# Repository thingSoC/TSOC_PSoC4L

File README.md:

# TSOC_PSoC4L - PSoC4 (Large) Embedded Module :

The TSOC_PSoC4L is a [PSoC4-Programmable System on Chip](http://www.cypress.com/documentation/datasheets/psoc-4-psoc-4200l-family-datasheet)
based board with integrated USB and Li-Po battery power and charging functions, 
in an Embedded Module format for the new thingSoC, Internet of Things open standard.

The TSOC_PSoC4L is a low cost, embeddable module featuring a PSoC4 "Large" device :

* 32-bit MCU Subsystem (48MHZ ARM Cortex-M0)
* USB Full-Speed Controller - 16 Endpoints
* Li-Po battery connector and integrated USB charger
* Programmable Analog Blocks (4 blocks)
* Programmable Digital Blocks (8 blocks)
* 3.3 Volt or 5.0 Volt Operation
* Serial Communication (3 Ports)
* Counter/Timers/PWMs (8 Ports)
* CAN (controller area network) Controller
* Battery Charge Status LED
* USER LED
* USER Pushbutton
* Optional 32Khz Oscillator for Real-Time Clock
* Optional High Precision Oscillator
* Optional FM24W256-G NVSRAM (32K Bytes Nonvolatile SRAM)
* [thingSoC Compliant Module](http://www.thingsoc.com)
* [Mikrobus Compatible Module](http://www.mikroe.com/mikrobus/) 

[TSOC_PSoC4L](https://github.com/thingSoC/TSOC_PSoC4L)

**thingSoC Reference Designs** are example thingSoC implementations that implement
various reference and testing circuits for demonstrating the use of the thingSoC libraries.
These reference designs can serve as starting templates for user designs.

---------------------------------------

## TSOC_PSoC4L Instructions

The TSOC_PSoC4L comes preprogrammed with a command line interpreter (CLI)
that runs on the enumerated USB COM port by default. It can be changed to
run onother ports interactively.

Immediately after plugging in the USB or Li-Po battery power the TSOC_PSoC4L will :

1) Runs a USB bootloader for ten (10) seconds to allow you to update the firmware.
   Use the [Cypress Bootloader Host](http://www.cypress.com/documentation/application-notes/an68272-psoc-3-psoc-4-psoc-5lp-and-psoc-analog-coprocessor-uart)
   to load new firmware into the device to customize it.

2) Runs the RSVP command line interpreter with the following commands :
  * commands : display the list of currenyl available commands
  * info : display the firmware revision number and other board details
  * echo : echo the current command
  * test adc : display all current ADC channel values
  * test uart : sends test string to all UART ports
  * test boot : run the bootloader
  * console x : changes the console to port "X"
  * connect x y : connect port x to port y until the user button is pressed to exit  
    where :  X (Y) = 
    0 - USB Port
    1 - UART1 Port
    2 - UART2 Port
    3 - I2C1 Port
    4 - I2C2 Port
    5 - SPI1 Port
    6 - SPI2 Port

---------------------------------------
## Other Applications

The TSOC_PSoC4L can also drive other devices, such as Servos, Motors, Relays and more.
This requires custom firmware at the current time.

---------------------------------------

## TSOC_PSoC4L Status <a name="TSOC_PSoC4L_status"/>

**11/06/2016:** 
Revision 1.0 - Initial Layout released to OSHpark

---------------------------------------
## TSOC_PSoC4L Model Images

[TSOC_PSoC4L](https://github.com/thingSoC/TSOC_PSoC4L)

[TSOC_PSoC4L](https://github.com/thingSoC/TSOC_PSoC4L)

---------------------------------------

## TSOC_PSoC4L Documentation Index <a name="TSOC_PSoC4L_documentation_index"/>

[TSOC_PSoC4L Project](http://thingsoc.github.io/projects/TSOC_PSoC4L.html)

[TSOC_PSoC4L Hardware](https://github.com/thingSoC/TSOC_PSoC4L/tree/master/TSOC_PSoC4L/hardware)

---------------------------------------

## thingSoC Documentation Index <a name="thingSoC_documentation_index"/>

[thingSoC Organization Website](http://thingSoC.github.io)

[thingSoC FAQ - Frequently Asked Questions](http://thingsoc.github.io/support/faq.html)

---------------------------------------

[ 
*thingSoC*](http://thingsoc.github.io)

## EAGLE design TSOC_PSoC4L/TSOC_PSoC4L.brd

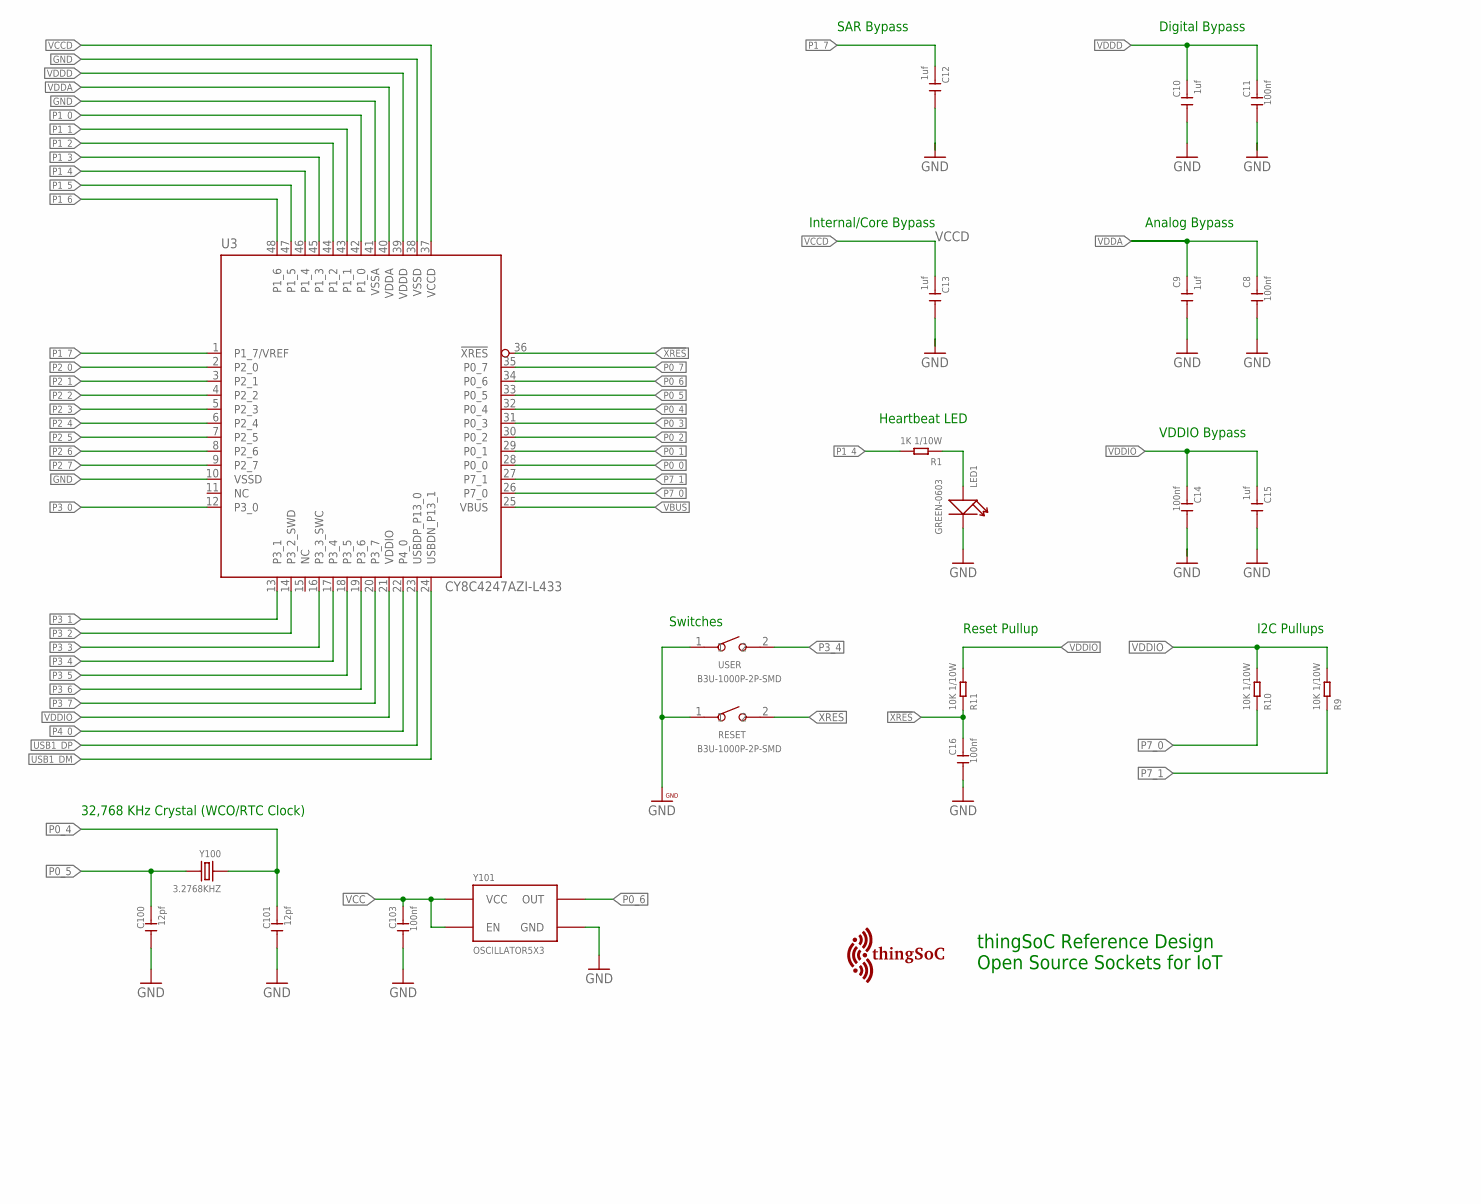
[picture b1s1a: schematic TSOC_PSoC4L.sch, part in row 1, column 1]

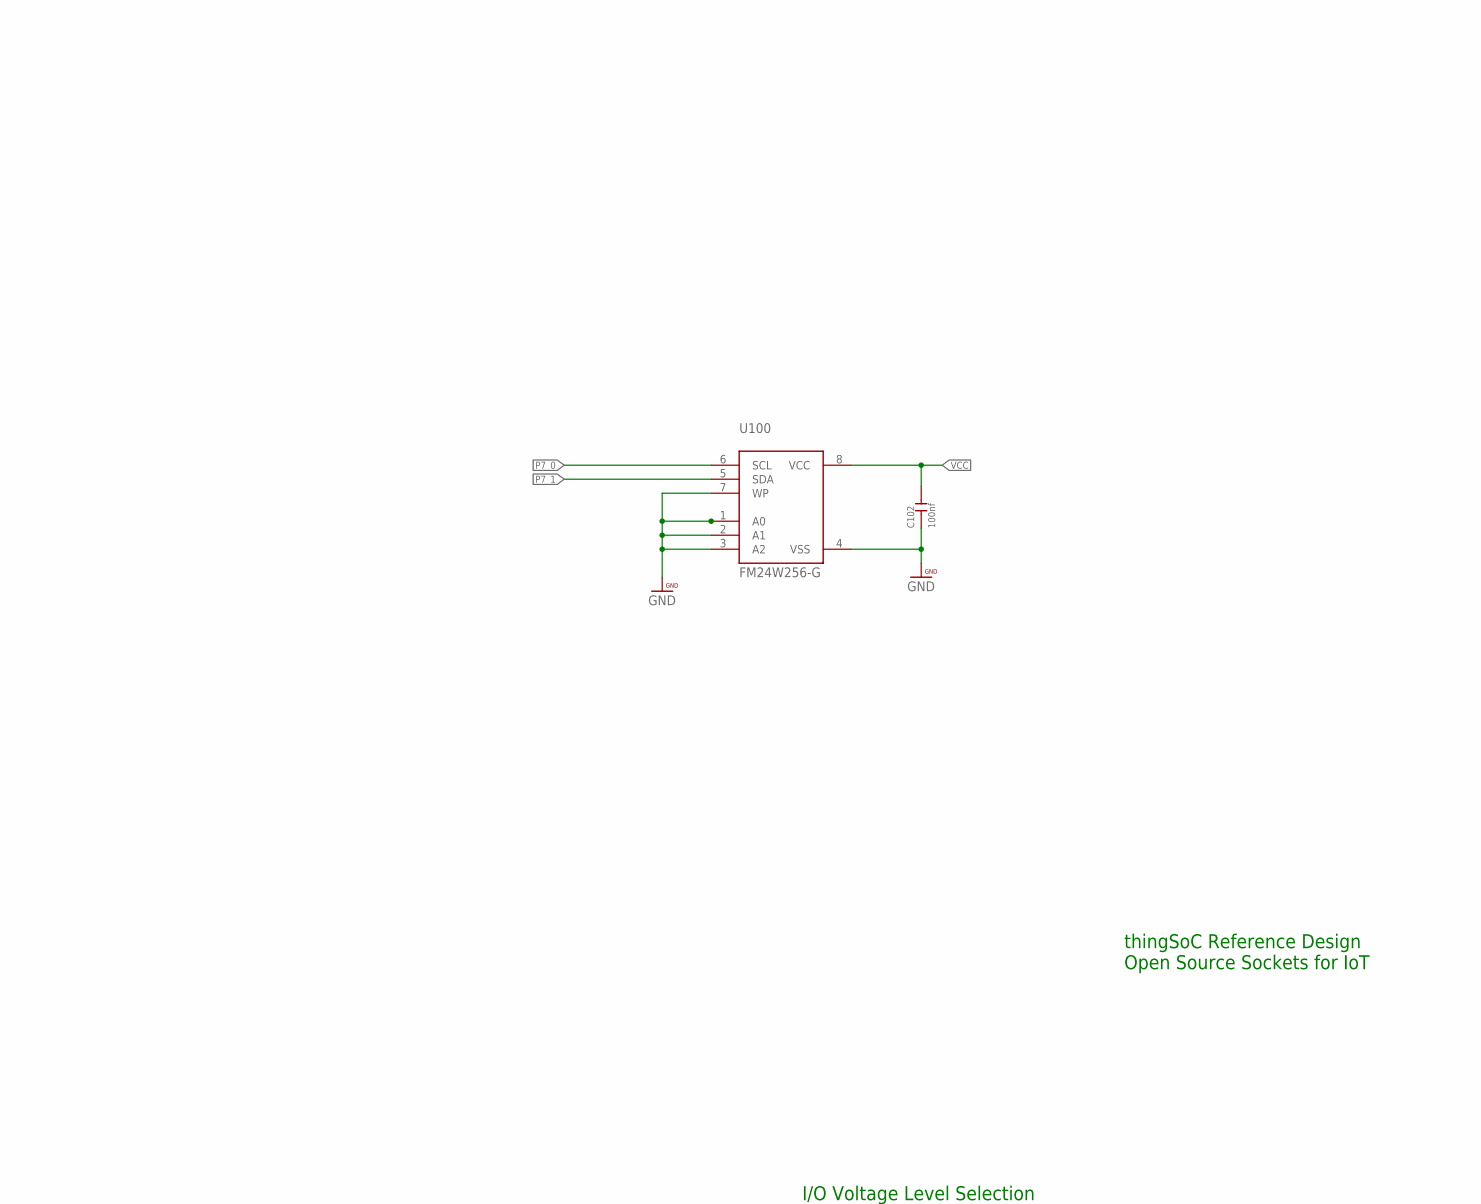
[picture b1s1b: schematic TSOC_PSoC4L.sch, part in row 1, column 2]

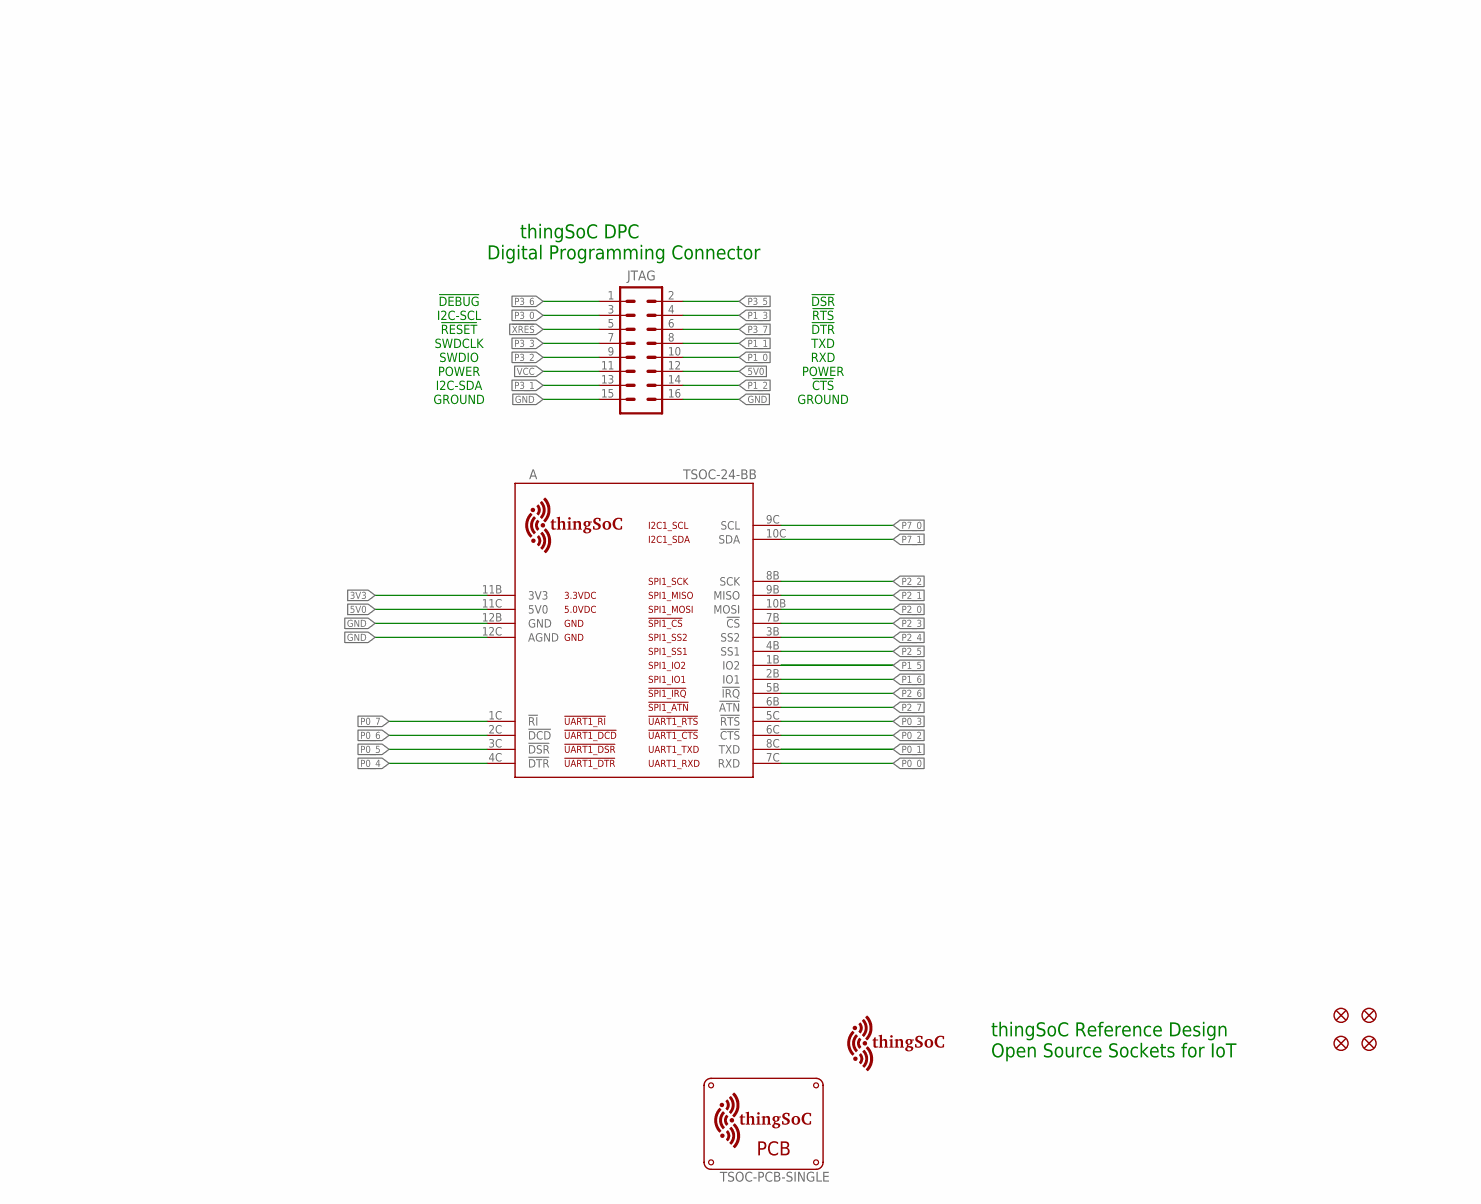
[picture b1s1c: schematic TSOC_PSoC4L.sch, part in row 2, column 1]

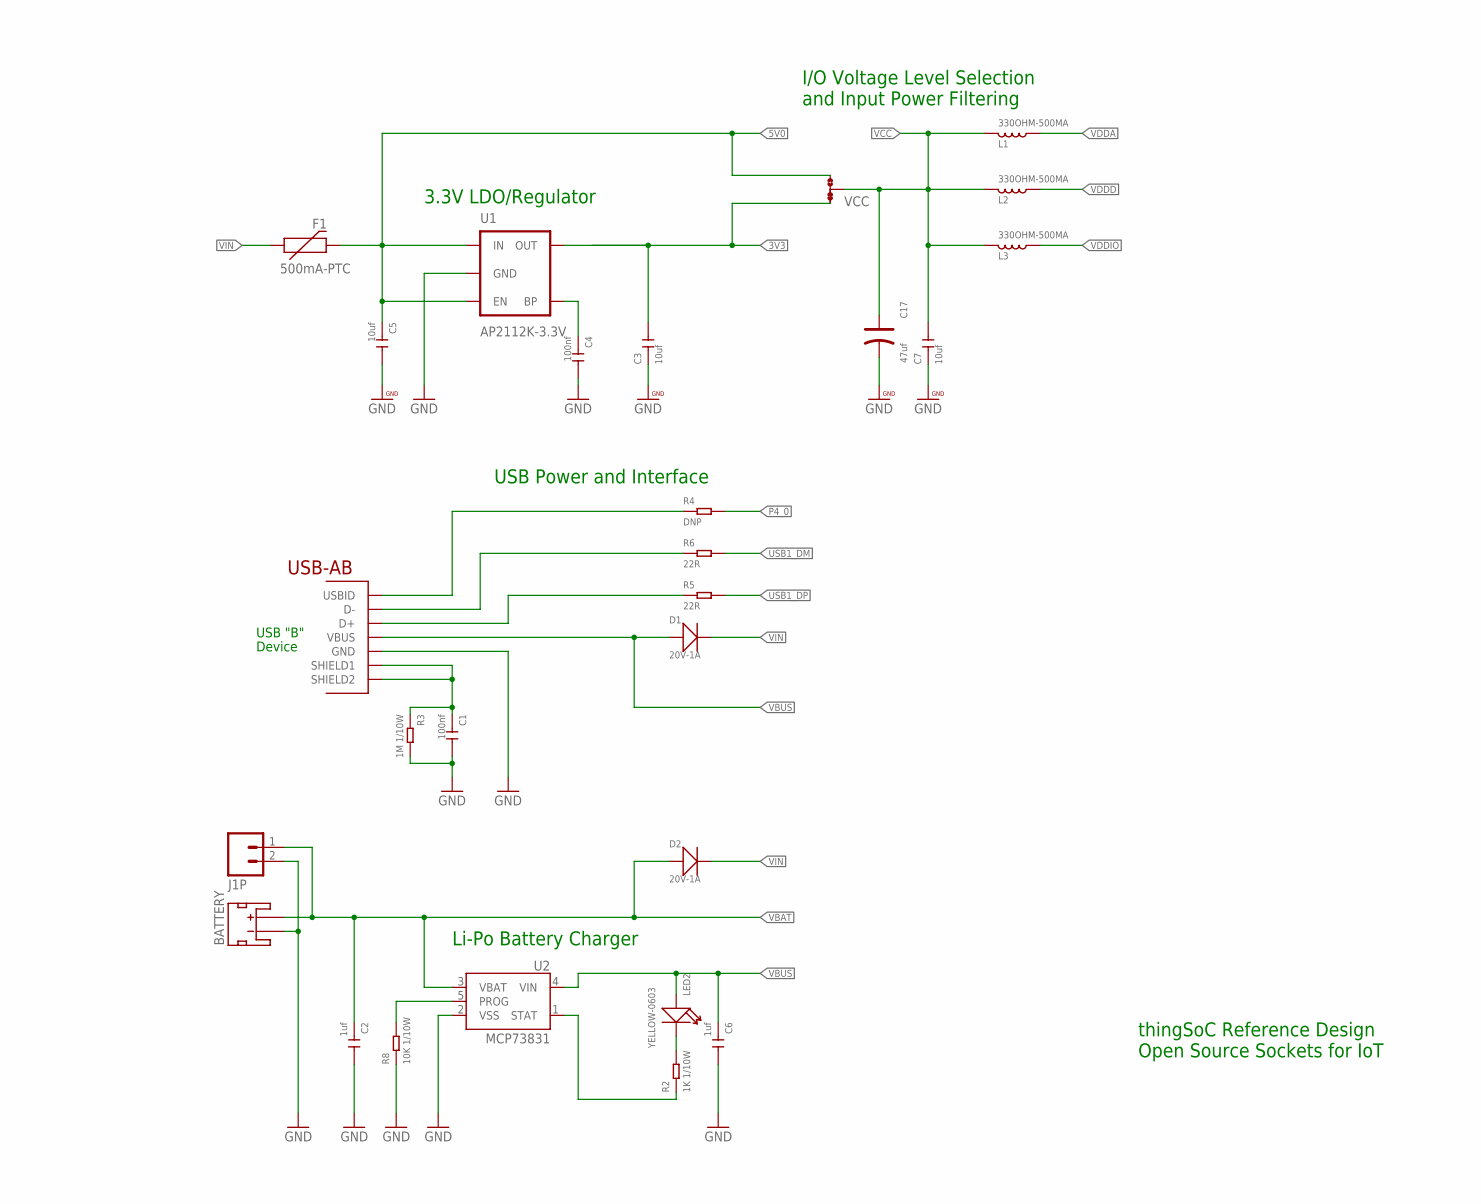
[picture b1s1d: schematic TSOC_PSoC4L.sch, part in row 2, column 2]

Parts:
A: TSOC-24-BB; TSOC-BB-S24
BATTERY: JST_2MM_MALE; JST-2-SMD
C1, C4, C8, C11, C14, C16, C102, C103: 100nf; C0603
C2, C6, C9, C10, C12, C13, C15: 1uf; C0603
C3, C5, C7: 10uf; C0603
C17: 47uf; AVX-A
C100, C101: 12pf; C0603
D1, D2: 20V-1A; SOD-123
F1: 500mA-PTC; PTC-1206
FID1, FID2, FID3, FID4: FIDUCIALUFIDUCIAL; MICRO-FIDUCIAL
J1P: M02-JST-2-PTH-NO_SILK; JST-2-PTH-NS
JTAG: M08X2; 2X8
L1, L2, L3: 330OHM-500MA; L0603
LED1: GREEN-0603; LED-0603
LED2: YELLOW-0603; LED-0603
R1, R2: 1K 1/10W; R0603
R3: 1M 1/10W; R0603
R4: DNP; R0603
R5, R6: 22R; R0603
R8, R9, R10, R11: 10K 1/10W; R0603
RESET: B3U-1000P-2P-SMD; SW2-2.6-3.0X2.5X1.2+0.4MM
U1: AP2112K-3.3V; SOT23-5
U2: MCP73831; SOT23-5
U3: CY8C4247AZI-L433; TQFP-7X7-48
U100: FM24W256-G; SO08
U$1: TSOC-PCB-SINGLE; TSOC-BB-BRD-DIM
U$100: TSOC-LOGO-LRG
U$101: TSOC-LOGO-SMALL; TSOC-LOGO-SML
USB: USB_AB; USB-AB-MICRO-SMD
USER: B3U-1000P-2P-SMD; SW2-2.6-3.0X2.5X1.2+0.4MM
VCC: JMP-3-1_2
Y100: 3.2768KHZ; X2-SMD-L2.0X1.2X0.55MM
Y101: OSCILLATOR5X3; CRYSTAL-SMD-5X3

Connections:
3V3: A.11B (3V3), C3.2, U1.5 (OUT), VCC.1
5V0: A.11C (5V0), C5.1, F1.2, JTAG.12, U1.1 (IN), U1.3 (EN), VCC.3
!XRES: C16.1, JTAG.5, R11.1, RESET.2, U3.36 (!XRES)
BYPASS1: C4.1, U1.4 (BP)
CLED: LED2.-, R2.2
CSTAT: R2.1, U2.1 (STAT)
GND: A.12B (GND), A.12C (AGND), BATTERY.1 (-), C1.2, C2.2, C3.1, C4.2, C5.2, C6.2, C7.1, C8.2, C9.2, C10.2, C11.2, C12.2, C13.2, C14.2, C15.2, C16.2, C17.-, C100.2, C101.2, C102.1, C103.2, J1P.2, JTAG.15, JTAG.16, LED1.-, R3.2, R8.1, RESET.1, U1.2 (GND), U2.2 (VSS), U3.10 (VSSD), U3.38 (VSSD), U3.41 (VSSA), U100.1 (A0), U100.2 (A1), U100.3 (A2), U100.4 (VSS), U100.7 (WP), USB.GND, USER.1, Y101.2 (GND)
unnamed: R8.2, U2.5 (PROG)
unnamed: LED1.+, R1.1
P0_0: A.7C (RXD), U3.28 (P0_0)
P0_1: A.8C (TXD), U3.29 (P0_1)
P0_2: A.6C (!CTS), U3.30 (P0_2)
P0_3: A.5C (!RTS), U3.31 (P0_3)
P0_4: A.4C (!DTR), C101.1, U3.32 (P0_4), Y100.1
P0_5: A.3C (!DSR), C100.1, U3.33 (P0_5), Y100.2
P0_6: A.2C (!DCD), U3.34 (P0_6), Y101.3 (OUT)
P0_7: A.1C (!RI), U3.35 (P0_7)
P1_0: JTAG.10, U3.42 (P1_0)
P1_1: JTAG.8, U3.43 (P1_1)
P1_2: JTAG.14, U3.44 (P1_2)
P1_3: JTAG.4, U3.45 (P1_3)
P1_4: R1.2, U3.46 (P1_4)
P1_5: A.1B (IO2), U3.47 (P1_5)
P1_6: A.2B (IO1), U3.48 (P1_6)
P1_7: C12.1, U3.1 (P1_7/VREF)
P2_0: A.10B (MOSI), U3.2 (P2_0)
P2_1: A.9B (MISO), U3.3 (P2_1)
P2_2: A.8B (SCK), U3.4 (P2_2)
P2_3: A.7B (!CS), U3.5 (P2_3)
P2_4: A.3B (SS2), U3.6 (P2_4)
P2_5: A.4B (SS1), U3.7 (P2_5)
P2_6: A.5B (!IRQ), U3.8 (P2_6)
P2_7: A.6B (!ATN), U3.9 (P2_7)
P3_0: JTAG.3, U3.12 (P3_0)
P3_1: JTAG.13, U3.13 (P3_1)
P3_2: JTAG.9, U3.14 (P3_2_SWD)
P3_3: JTAG.7, U3.16 (P3_3_SWC)
P3_4: U3.17 (P3_4), USER.2
P3_5: JTAG.2, U3.18 (P3_5)
P3_6: JTAG.1, U3.19 (P3_6)
P3_7: JTAG.6, U3.20 (P3_7)
P4_0: R4.2, U3.22 (P4_0)
P7_0: A.9C (SCL), R10.1, U3.26 (P7_0), U100.6 (SCL)
P7_1: A.10C (SDA), R9.1, U3.27 (P7_1), U100.5 (SDA)
USB1_DM: R6.2, U3.24 (USBDN_P13_1)
USB1_DP: R5.2, U3.23 (USBDP_P13_0)
USB1_I: R4.1, USB.ID (USBID)
USB1_M: R6.1, USB.D-
USB1_P: R5.1, USB.D+
USB1_SHIELD: C1.1, R3.1, USB.SHIELD1, USB.SHIELD2
VBAT: BATTERY.2 (+), C2.1, D2.+, J1P.1, U2.3 (VBAT)
VBUS: C6.1, D1.+, LED2.+, U2.4 (VIN), U3.25 (VBUS), USB.VBUS
VCC: C7.2, C17.+, C102.2, C103.1, JTAG.11, L1.1, L2.1, L3.1, U100.8 (VCC), VCC.2, Y101.1 (EN), Y101.4 (VCC)
VCCD: C13.1, U3.37 (VCCD)
VDDA: C8.1, C9.1, L1.2, U3.40 (VDDA)
VDDD: C10.1, C11.1, L2.2, U3.39 (VDDD)
VDDIO: C14.1, C15.1, L3.2, R9.2, R10.2, R11.2, U3.21 (VDDIO)
VIN: D1.-, D2.-, F1.1

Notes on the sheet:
Internal/Core Bypass
Digital Bypass
VDDIO Bypass
SAR Bypass
USB "B"
Device
3.3V LDO/Regulator
Reset Pullup
Heartbeat LED
Analog Bypass
Li-Po Battery Charger
USB Power and Interface
I/O Voltage Level Selection and Input Power Filtering
I2C Pullups
thingSoC Reference Design Open Source Sockets for IoT
I2C-SDA
I2C-SCL
!RESET
SWDCLK
SWDIO
POWER
GROUND
!DEBUG
!DSR
!RTS
!CTS
!DTR
TXD
RXD
thingSoC DPC Digital Programming Connector
Switches
32,768 KHz Crystal (WCO/RTC Clock)

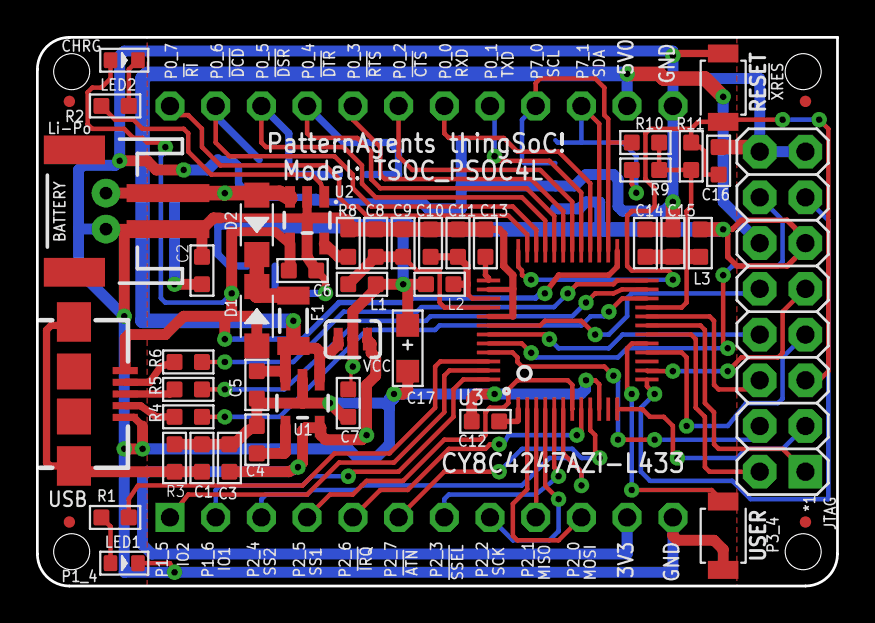
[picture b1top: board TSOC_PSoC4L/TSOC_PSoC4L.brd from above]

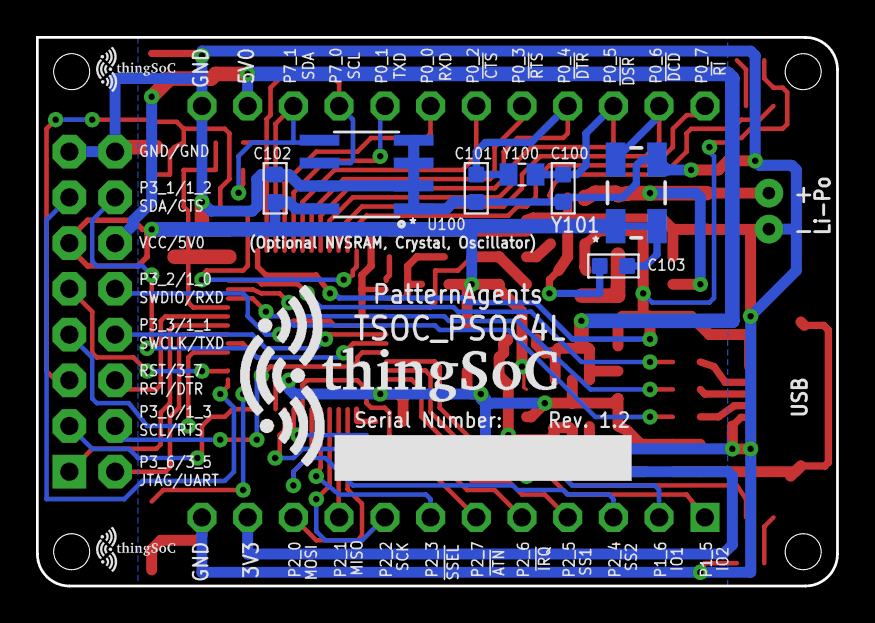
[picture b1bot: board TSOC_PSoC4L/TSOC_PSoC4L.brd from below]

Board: 2 copper layers, 44.5 x 30.5 mm, 61 parts (11 on the bottom side), 58 nets.

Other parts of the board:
U$102: TSOC-LOGO-SMALL; TSOC-LOGO-SML

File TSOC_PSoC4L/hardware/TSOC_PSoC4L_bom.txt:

Partlist exported from U:/PatternAgents/eagle/TSOC_Modules/TSOC_PSoC4L/TSOC_PSoC4L/revisions/REV1_0/TSOC_PSoC4L.sch at 11/17/2016 4:03:40 PM

Qty Value             Device                                                Package                   Parts                           Description                                                                                                   
1                     JST_2MM_MALE                                          JST-2-SMD                 BATTERY                         Mates to single-cell LiPo batteries.                                                                          
1                     M02-JST-2-PTH-NO_SILK                                 JST-2-PTH-NS              J1P                             Standard 2-pin 0.1" header. Use with                                                                          
1                     M08X2                                                 2X8                       JTAG                            .1" headers, two rows of 8 each                                                                               
7   100nf             CERAMIC-100NF-50V-10%-X7R(0603)                       C0603                     C1, C4, C8, C11, C14, C16, C102 302010138                                                                                                     
4   10K 1/10W         SMD-RES-10K-5%-1/10W(0603)                            R0603                     R8, R9, R10, R11                301010293                                                                                                     
3   10uf              CERAMIC-10UF-10V-10%-X5R(0603)                        C0603                     C3, C5, C7                      302010103                                                                                                     
2   12pf              CERAMIC-12PF-50V-5%-NPO(0603)                         C0603                     C100, C101                      302010067                                                                                                     
2   1K 1/10W          SMD-RES-1K-5%-1/10W(0603)                             R0603                     R1, R2                          301010291 
2   0 1/10W           SMD-RES-0-5%-1/10W(0603)                              R0603                     R7 
1   1M 1/10W          SMD-RES-1M-5%-1/10W(0603)                             R0603                     R3                              301010100                                                                                                     
7   1uf               CERAMIC-1UF-25V-10%-X7R(0603)                         C0603                     C2, C6, C9, C10, C12, C13, C15  302010139                                                                                                     
2   20V-1A            SMD-DIODE-SCHOTTKY-20V-1A(SOD-123)                    SOD-123                   D1, D2                          304020034                                                                                                     
2   22R               SMD-RES-22R-5%-1/10W(0603)                            R0603                     R5, R6                          301010289                                                                                                     
1   3.2768KHZ         SMD-CRYSTAL-32.768KHZ-12.5PF-20PPM-90K(2P-L2.0X1.2MM) X2-SMD-L2.0X1.2X0.55MM    Y100                            306010020                                                                                                     
3   330OHM-500MA      SMD-FERRITE-CHIP-120-OHM-500MA(0603)                  L0603                     L1, L2, L3                      303030001                                                                                                     
1   500mA-PTC         PTCSMD                                                PTC-1206                  F1                              Resettable Fuse PTC                                                                                           
1   AP2112K-3.3V      V_REG_LDOSMD                                          SOT23-5                   U1                              Voltage Regulator LDO                                                                                         
2   B3U-1000P-2P-SMD  SMD-BUTTON(2P-3.0X2.5X1.2+0.4MM)-B3U-1000P-2P-SMD     SW2-2.6-3.0X2.5X1.2+0.4MM RESET, USER                     311020047                                                                                                     
1   CY8C4247AZI-L433  CY8C4247AZI-L433                                      TQFP-7X7-48               U3                              Cypress PSoC® 4 - Programmable System on Chip,  Cortex-M0 Based : USB Version!                                
1   DNP               SMD-RES-22R-5%-1/10W(0603)                            R0603                     R4                              301010289                                                                                                     
4   FIDUCIALUFIDUCIAL FIDUCIALUFIDUCIAL                                     MICRO-FIDUCIAL            FID1, FID2, FID3, FID4          Fiducial Alignment Points                                                                                     
1   FM24W256-G        FM24W256-G                                            SO08                      U100                            I2C FRAM FM24W256                                                                                             
1   GREEN-0603        SMD-LED-CLEAR-GREEN(0603)                             LED-0603                  LED1                            304090043                                                                                                     
1   JMP-3-1_2         JMP-3-1_2                                             JMP-3-1_2                 VCC                             Three Terminal Jumper - 1 & 2 Connected                                                                       
1   MCP73831          MCP73831                                              SOT23-5                   U2                              Miniature single cell, fully integrated Li-Ion, Li-polymer charge management controller                       
1   OSCILLATOR5X3     OSCILLATOR5X3                                         CRYSTAL-SMD-5X3           OSC                             Generic 5x3 and 7x5 oscillators                                                                               
1   USB_AB            USB_AB                                                USB-AB-MICRO-SMD          USB                             This is a USB AB connector that is compatible with USB OTG. i.e. this connector can serve as a host or device 
1   YELLOW-0603       SMD-LED-CLEAR-YELLOW(0603)                            LED-0603                  LED2                            304090044

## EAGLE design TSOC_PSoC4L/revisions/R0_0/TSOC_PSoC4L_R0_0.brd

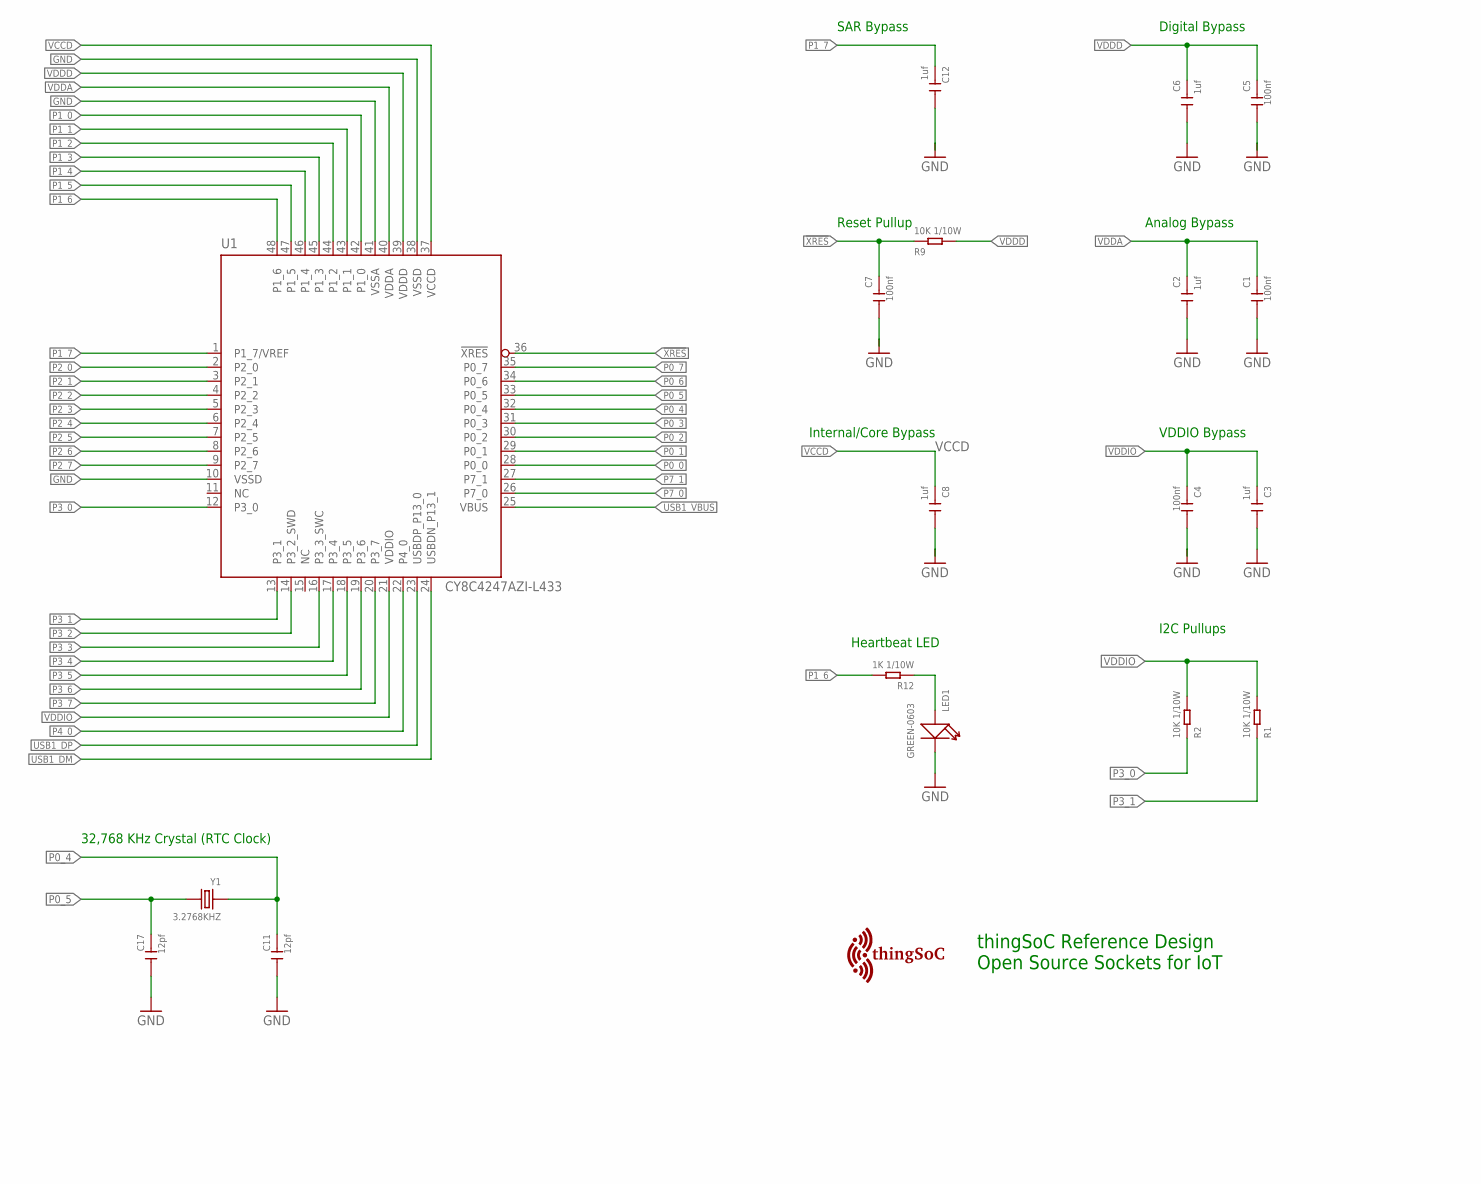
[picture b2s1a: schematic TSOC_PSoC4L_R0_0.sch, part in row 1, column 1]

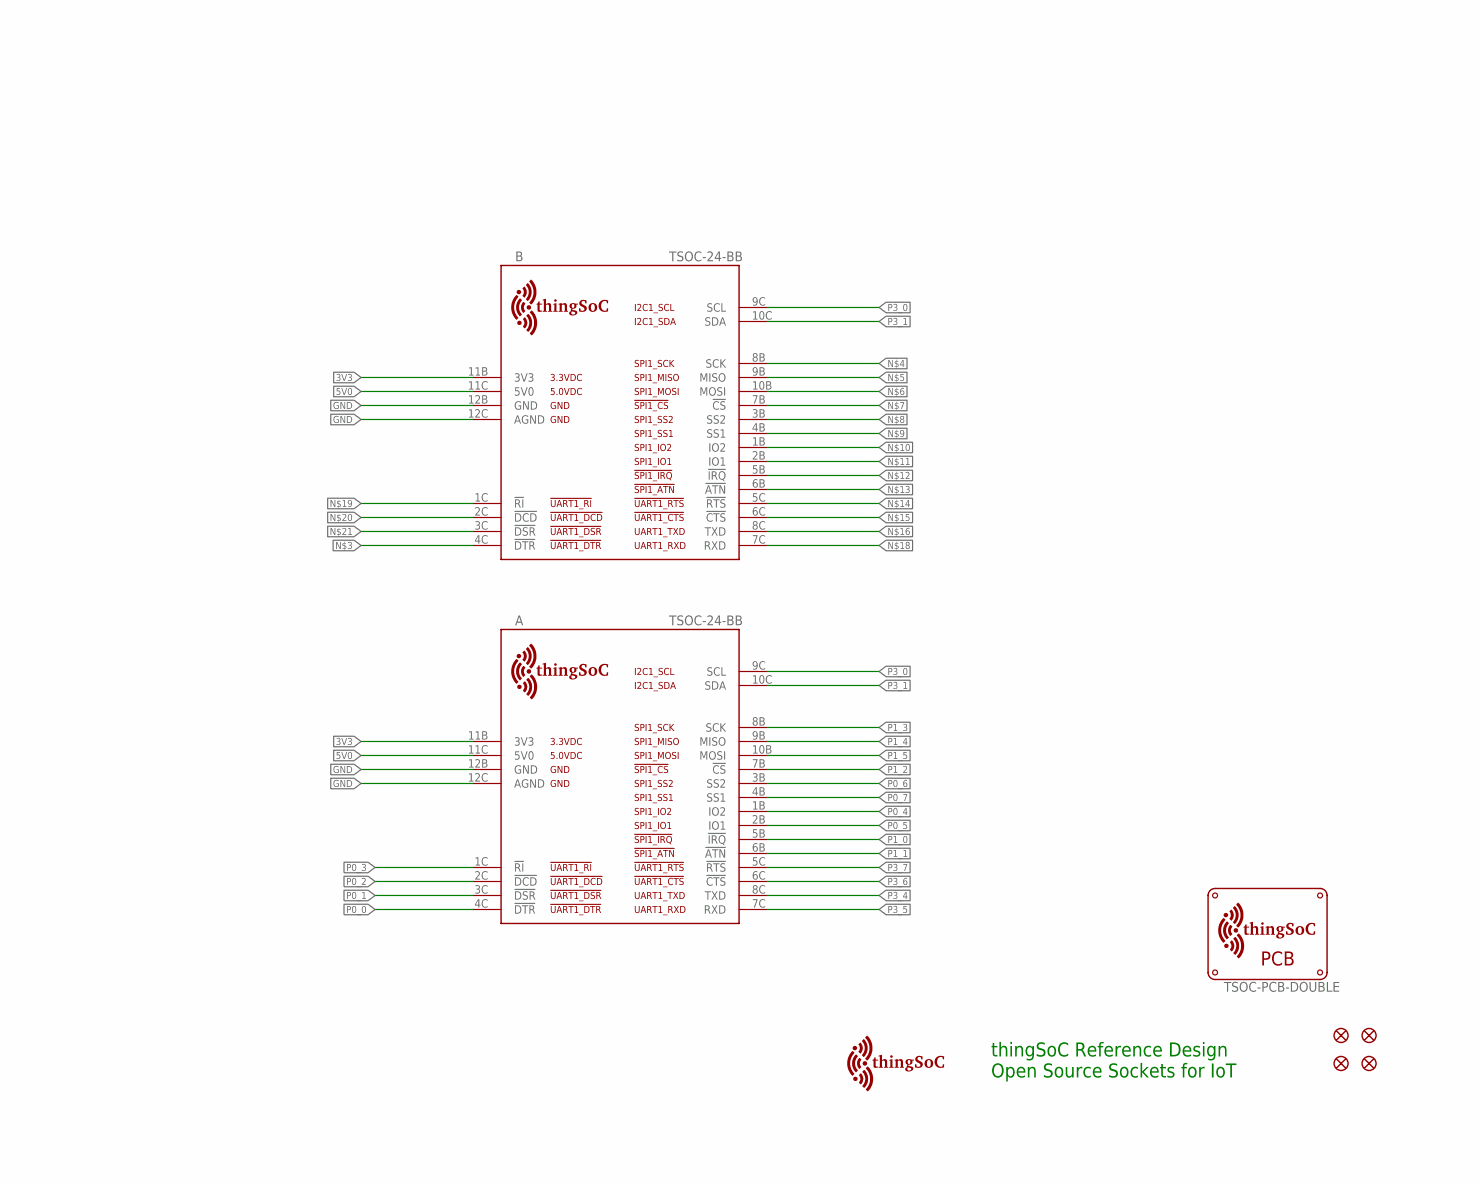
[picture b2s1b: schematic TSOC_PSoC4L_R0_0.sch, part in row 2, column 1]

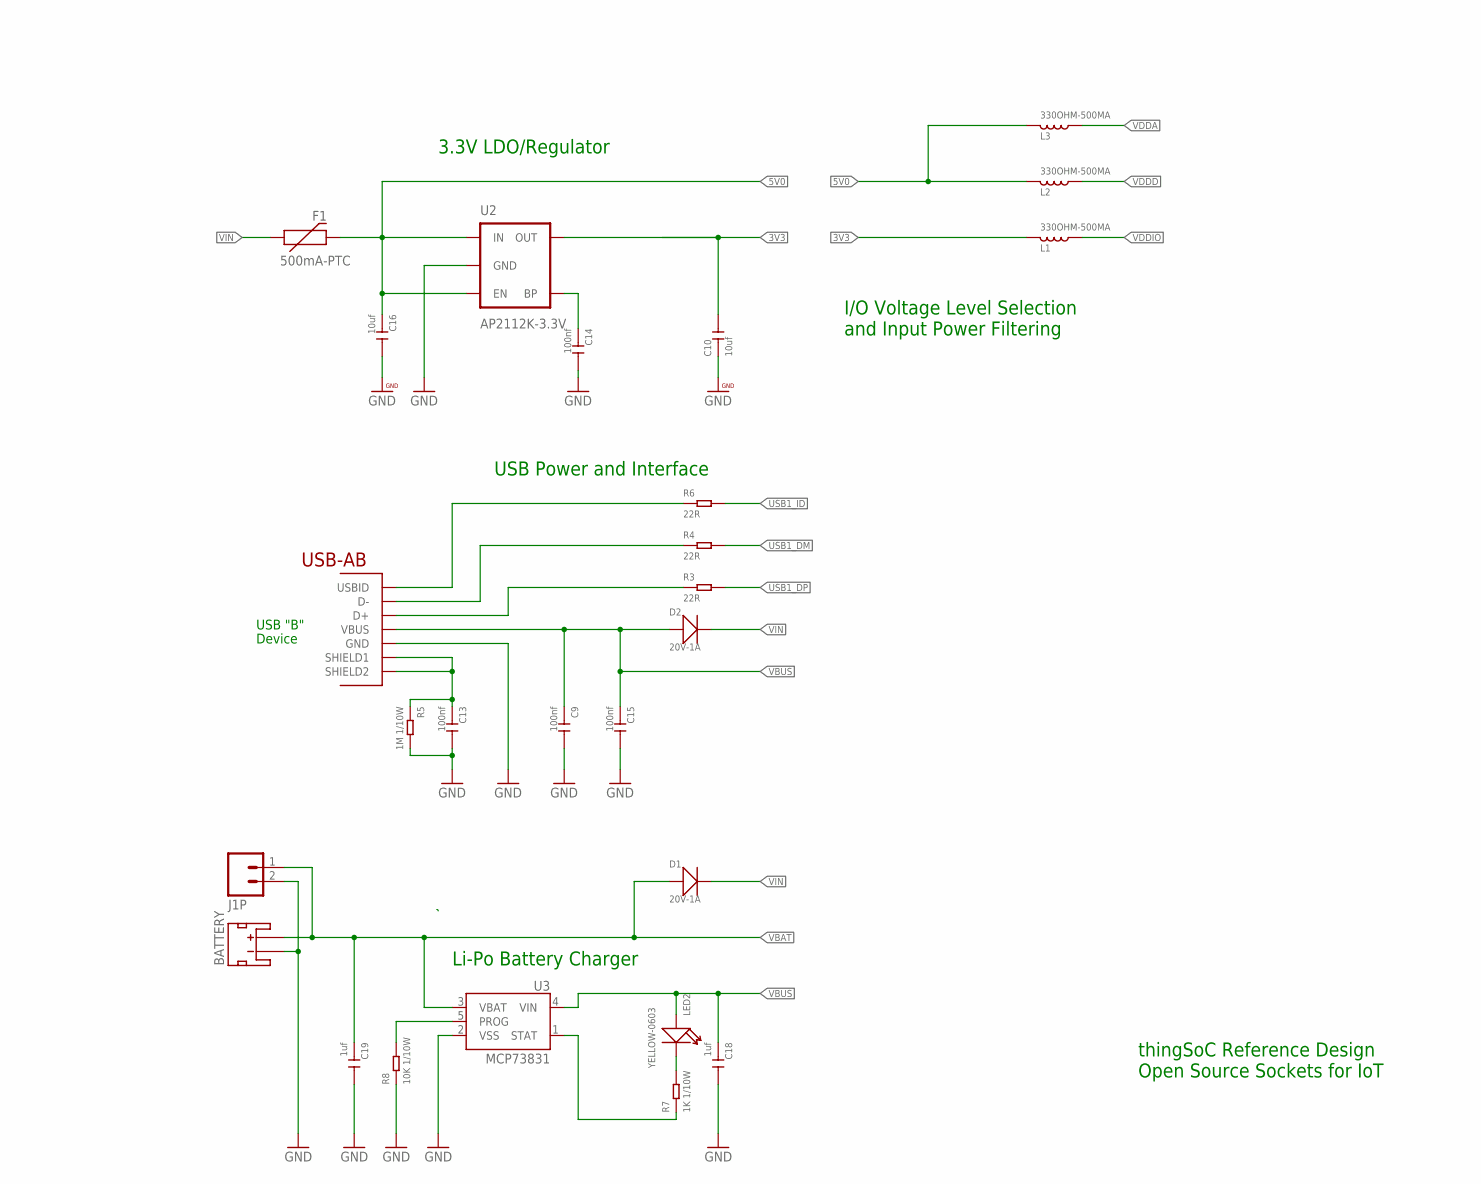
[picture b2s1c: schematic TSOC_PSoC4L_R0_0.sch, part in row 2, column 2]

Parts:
A: TSOC-24-BB; TSOC-BB-S24
B: TSOC-24-BB; TSOC-BB-S24
BATTERY: JST_2MM_MALE; JST-2-SMD
C1, C4, C5, C7, C9, C13, C14, C15: 100nf; C0603
C2, C3, C6, C8, C12, C18, C19: 1uf; C0603
C10, C16: 10uf; C0603
C11, C17: 12pf; C0603
D1, D2: 20V-1A; SOD-123
F1: 500mA-PTC; PTC-1206
FID1, FID2, FID3, FID4: FIDUCIALUFIDUCIAL; MICRO-FIDUCIAL
J1P: M02-JST-2-PTH-NO_SILK; JST-2-PTH-NS
L1, L2, L3: 330OHM-500MA; L0603
LED1: GREEN-0603; LED-0603
LED2: YELLOW-0603; LED-0603
R1, R2, R8, R9: 10K 1/10W; R0603
R3, R4, R6: 22R; R0603
R5: 1M 1/10W; R0603
R7, R12: 1K 1/10W; R0603
U1: CY8C4247AZI-L433; TQFP-7X7-48
U2: AP2112K-3.3V; SOT23-5
U3: MCP73831; SOT23-5
U$1: TSOC-PCB-DOUBLE; TS0C-BB-BRD-DBL-DIM
U$100: TSOC-LOGO-SMALL; TSOC-LOGO-SML
U$101: TSOC-LOGO-LRG
USB: USB_AB; USB-AB-MICRO-SMD
Y1: 3.2768KHZ; X2-SMD-L2.0X1.2X0.55MM

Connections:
3V3: A.11B (3V3), B.11B (3V3), C10.2, L1.1, U2.5 (OUT)
5V0: A.11C (5V0), B.11C (5V0), C16.1, F1.2, L2.1, L3.1, U2.1 (IN), U2.3 (EN)
!XRES: C7.1, R9.1, U1.36 (!XRES)
BYPASS1: C14.1, U2.4 (BP)
CLED: LED2.-, R7.2
CSTAT: R7.1, U3.1 (STAT)
GND: A.12B (GND), A.12C (AGND), B.12B (GND), B.12C (AGND), BATTERY.1 (-), C1.2, C2.2, C3.2, C4.2, C5.2, C6.2, C7.2, C8.2, C9.2, C10.1, C11.2, C12.2, C13.2, C14.2, C15.2, C16.2, C17.2, C18.2, C19.2, J1P.2, LED1.-, R5.2, R8.1, U1.10 (VSSD), U1.38 (VSSD), U1.41 (VSSA), U2.2 (GND), U3.2 (VSS), USB.GND
unnamed: R8.2, U3.5 (PROG)
unnamed: LED1.+, R12.1
P0_0: A.4C (!DTR), U1.28 (P0_0)
P0_1: A.3C (!DSR), U1.29 (P0_1)
P0_2: A.2C (!DCD), U1.30 (P0_2)
P0_3: A.1C (!RI), U1.31 (P0_3)
P0_4: A.1B (IO2), C11.1, U1.32 (P0_4), Y1.1
P0_5: A.2B (IO1), C17.1, U1.33 (P0_5), Y1.2
P0_6: A.3B (SS2), U1.34 (P0_6)
P0_7: A.4B (SS1), U1.35 (P0_7)
P1_0: A.5B (!IRQ), U1.42 (P1_0)
P1_1: A.6B (!ATN), U1.43 (P1_1)
P1_2: A.7B (!CS), U1.44 (P1_2)
P1_3: A.8B (SCK), U1.45 (P1_3)
P1_4: A.9B (MISO), U1.46 (P1_4)
P1_5: A.10B (MOSI), U1.47 (P1_5)
P1_6: R12.2, U1.48 (P1_6)
P1_7: C12.1, U1.1 (P1_7/VREF)
P2_0: U1.2 (P2_0)
P2_1: U1.3 (P2_1)
P2_2: U1.4 (P2_2)
P2_3: U1.5 (P2_3)
P2_4: U1.6 (P2_4)
P2_5: U1.7 (P2_5)
P2_6: U1.8 (P2_6)
P2_7: U1.9 (P2_7)
P3_0: A.9C (SCL), B.9C (SCL), R2.1, U1.12 (P3_0)
P3_1: A.10C (SDA), B.10C (SDA), R1.1, U1.13 (P3_1)
P3_2: U1.14 (P3_2_SWD)
P3_3: U1.16 (P3_3_SWC)
P3_4: A.8C (TXD), U1.17 (P3_4)
P3_5: A.7C (RXD), U1.18 (P3_5)
P3_6: A.6C (!CTS), U1.19 (P3_6)
P3_7: A.5C (!RTS), U1.20 (P3_7)
P4_0: U1.22 (P4_0)
P7_0: U1.26 (P7_0)
P7_1: U1.27 (P7_1)
USB1_DM: R4.2, U1.24 (USBDN_P13_1)
USB1_DP: R3.2, U1.23 (USBDP_P13_0)
USB1_I: R6.1, USB.ID (USBID)
USB1_ID: R6.2
USB1_M: R4.1, USB.D-
USB1_P: R3.1, USB.D+
USB1_SHIELD: C13.1, R5.1, USB.SHIELD1, USB.SHIELD2
USB1_VBUS: U1.25 (VBUS)
VBAT: BATTERY.2 (+), C19.1, D1.+, J1P.1, U3.3 (VBAT)
VBUS: C9.1, C15.1, C18.1, D2.+, LED2.+, U3.4 (VIN), USB.VBUS
VCCD: C8.1, U1.37 (VCCD)
VDDA: C1.1, C2.1, L3.2, U1.40 (VDDA)
VDDD: C5.1, C6.1, L2.2, R9.2, U1.39 (VDDD)
VDDIO: C3.1, C4.1, L1.2, R1.2, R2.2, U1.21 (VDDIO)
VIN: D1.-, D2.-, F1.1

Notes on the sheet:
Internal/Core Bypass
Digital Bypass
VDDIO Bypass
SAR Bypass
USB "B"
Device
3.3V LDO/Regulator
Reset Pullup
Heartbeat LED
Analog Bypass
Li-Po Battery Charger
USB Power and Interface
I/O Voltage Level Selection and Input Power Filtering
I2C Pullups
32,768 KHz Crystal (RTC Clock)
thingSoC Reference Design Open Source Sockets for IoT

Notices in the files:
parts and their libraries:
thingSoC: License : http://creativecommons.org/licenses/by-sa/4.0
(Creative Commons 4.0)
PatternAgents-Cypress: License : http://creativecommons.org/licenses/by-sa/3.0
(Creative Commons 3.0)
